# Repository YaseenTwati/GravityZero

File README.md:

# GravityZero

GravityZero is an Open Source STM32G473-based development board with two USB ports (Native & CH340 Serial), and access to nearly all the IO ports through the headers. alongside an onboard "NeoPixel" RGB LED.

More can be learned about it in my [Write Up Here](https://yaseen.ly/stm32g473-development-board-gravityzero/).

### Should you build one ?
Most probably not no, the microcontroller isn't cheap ( at the time of writing ), the pcb is 4 layer pcb which can most likely be reduced down to two, and there plenety of cheaper options out there.
This was designed for the experience & fun, which again you can learn more about in my write up.

---
### License 
<br />This work is licensed under a <a rel="license" href="http://creativecommons.org/licenses/by-sa/4.0/">Creative Commons Attribution-ShareAlike 4.0 International License</a>.

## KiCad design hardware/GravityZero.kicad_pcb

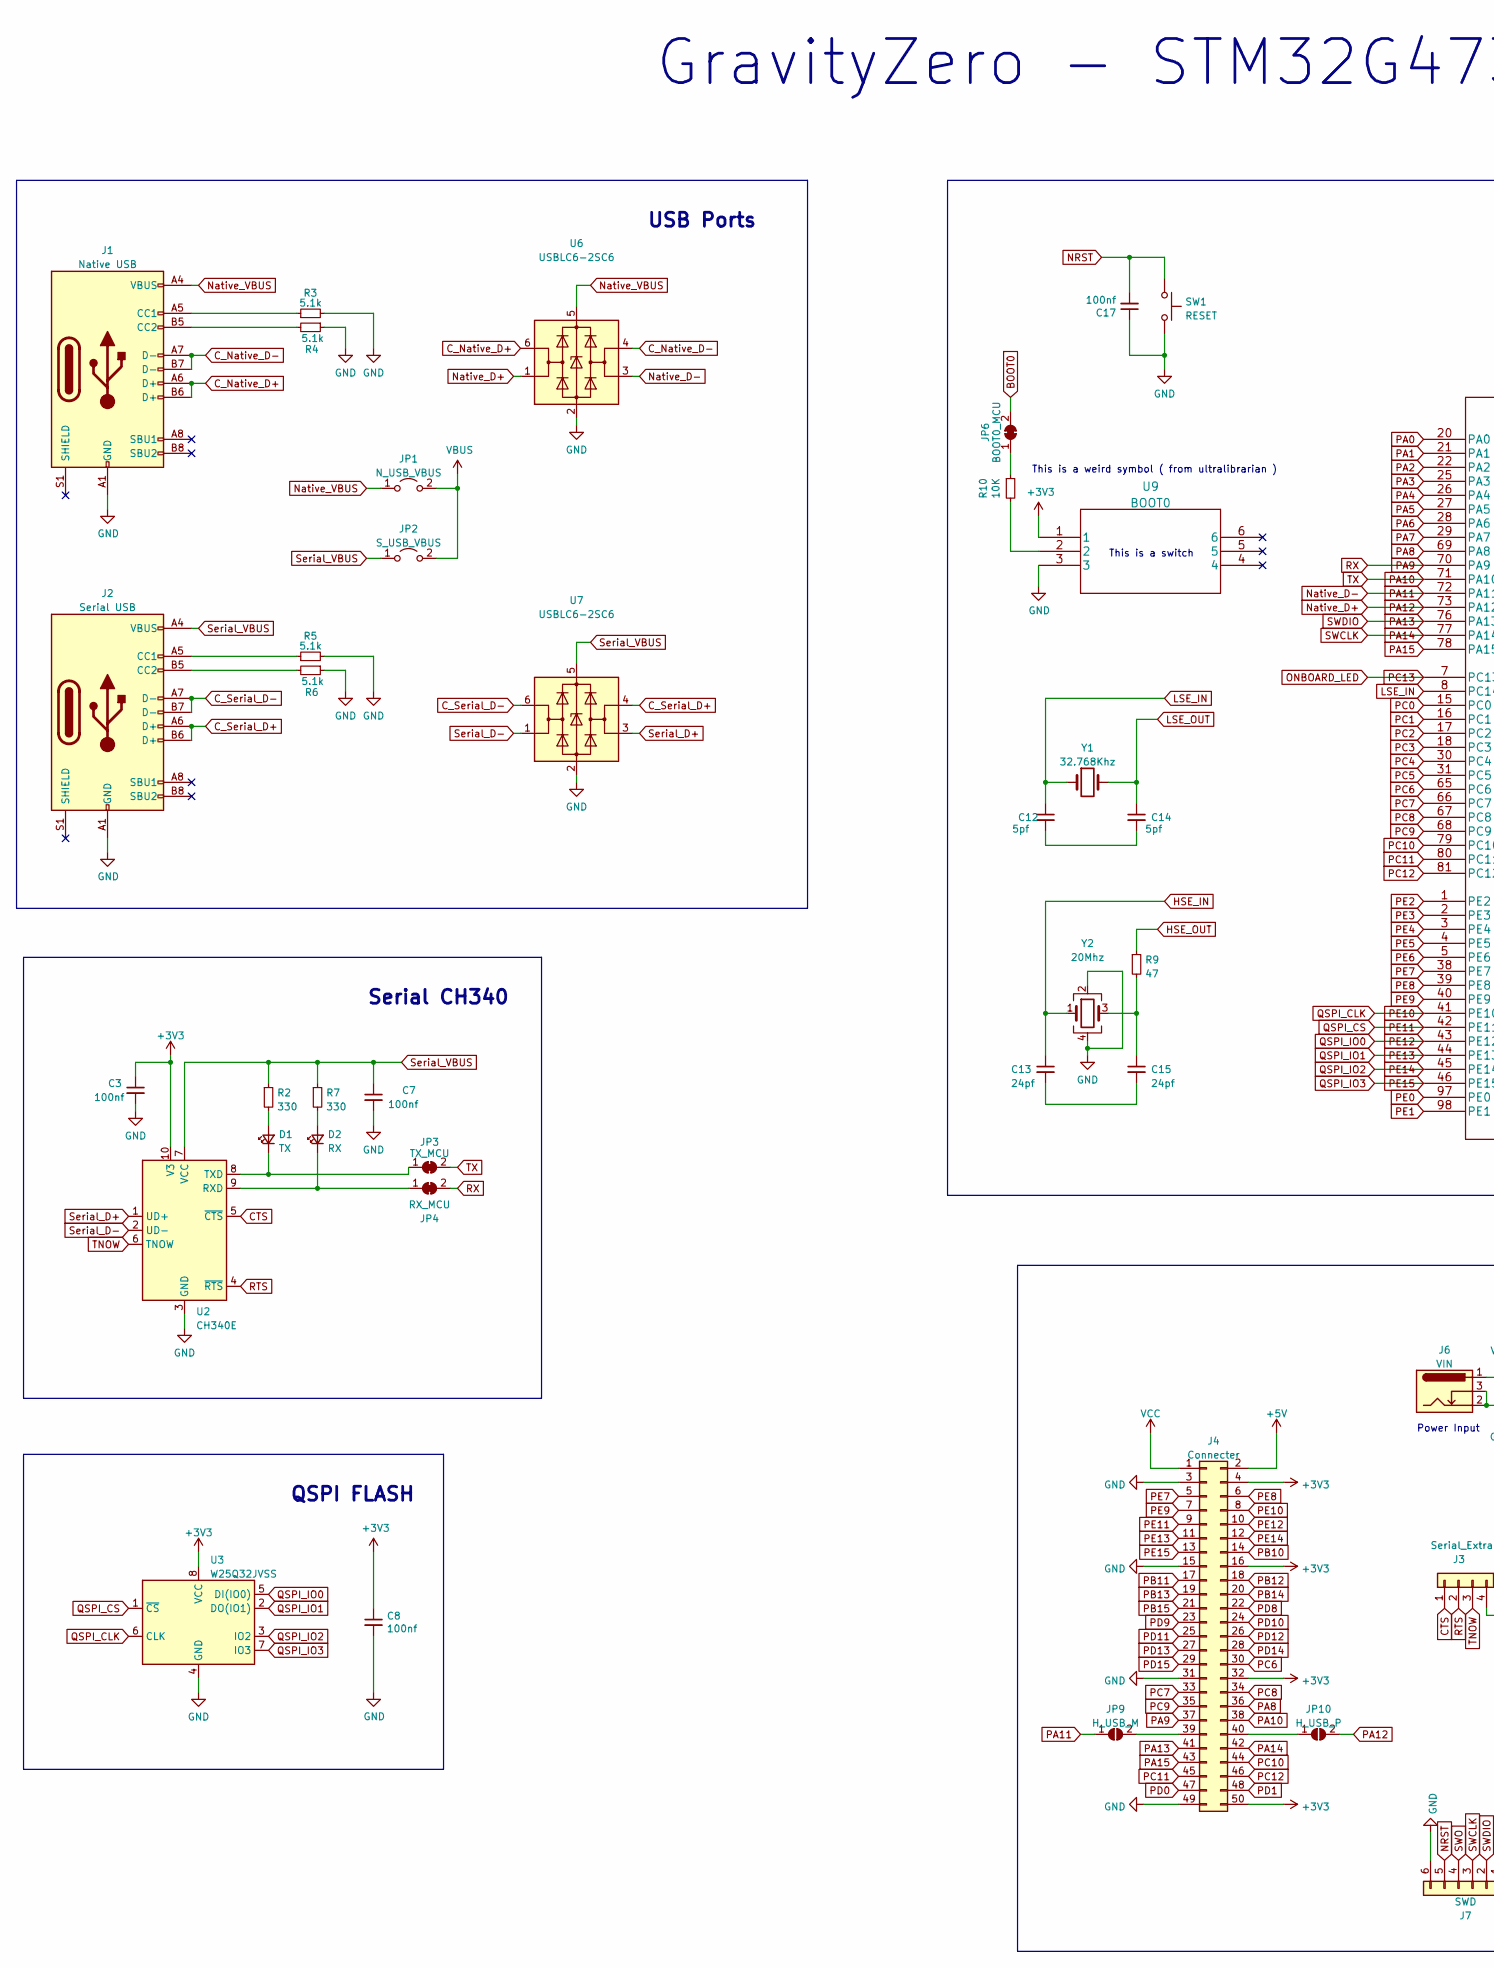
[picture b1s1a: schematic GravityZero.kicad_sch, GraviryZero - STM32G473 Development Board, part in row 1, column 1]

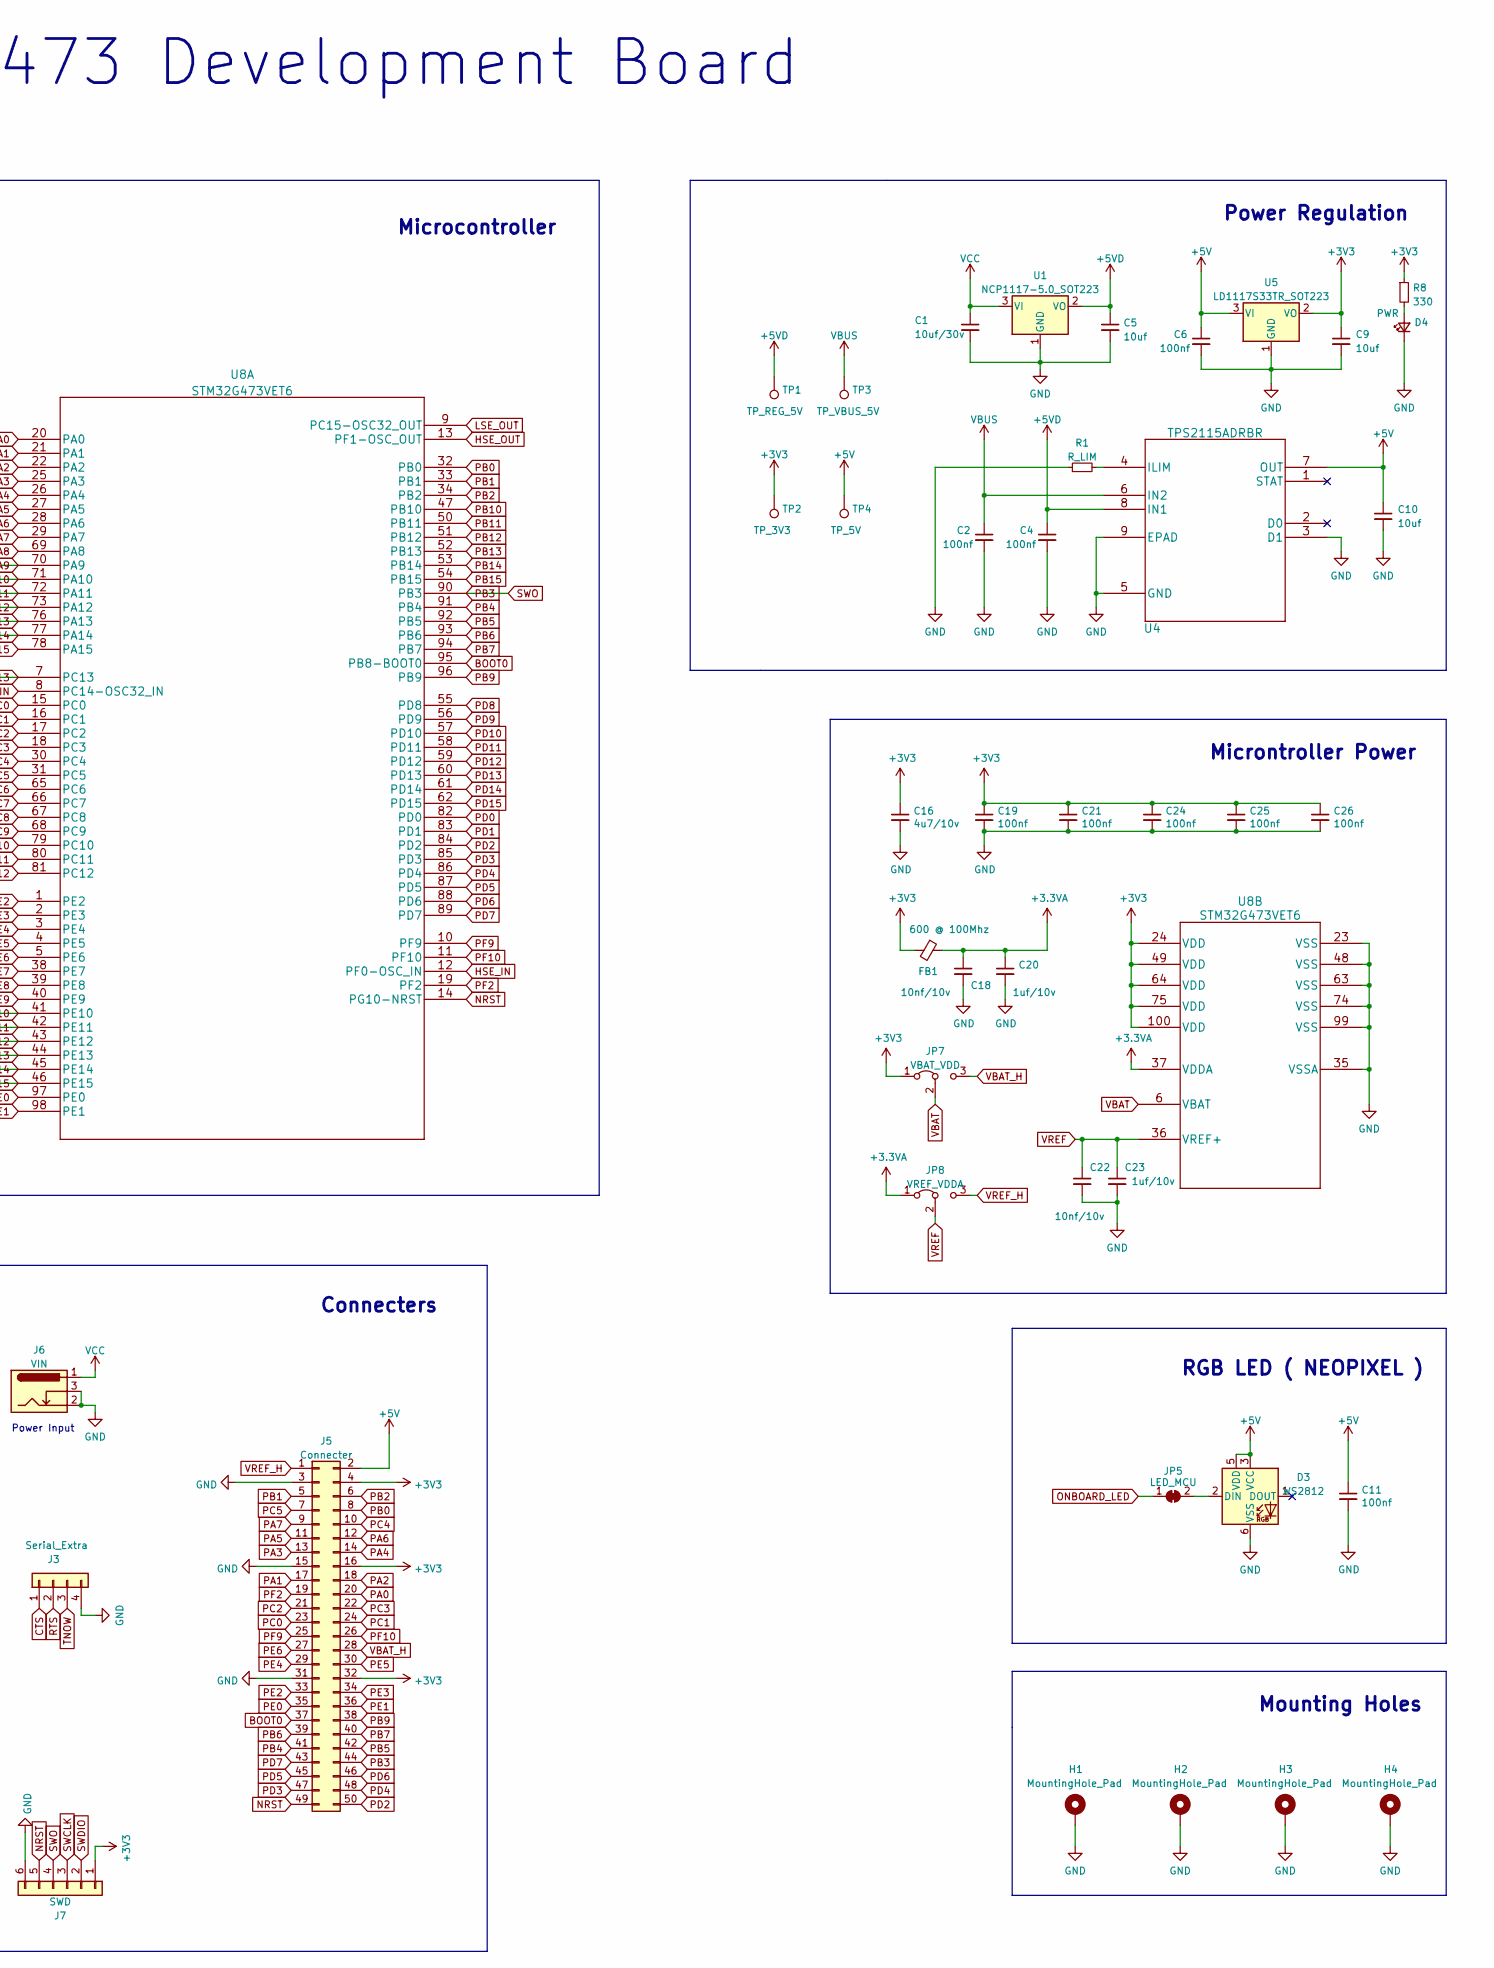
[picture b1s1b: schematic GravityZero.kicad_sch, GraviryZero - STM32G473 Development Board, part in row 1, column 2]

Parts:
C1: 10uf/30v; C_0805_2012Metric
C2, C3, C4, C6, C7, C8, C11, C17, C19, C21, C24, C25, C26: 100nf; C_0603_1608Metric
C5, C9, C10: 10uf; C_0603_1608Metric
C12, C14: 5pf; C_0603_1608Metric
C13, C15: 24pf; C_0603_1608Metric
C16: 4u7/10v; C_0603_1608Metric
C18, C22: 10nf/10v; C_0603_1608Metric
C20, C23: 1uf/10v; C_0603_1608Metric
D1: TX; LED_0603_1608Metric
D2: RX; LED_0603_1608Metric
D3: WS2812; LED_WS2812_PLCC6_5.0x5.0mm_P1.6mm
D4: PWR; LED_0603_1608Metric
FB1: 600 @ 100Mhz; L_0603_1608Metric
H1, H2, H3, H4: MountingHole_Pad; MountingHole_3.2mm_M3_Pad_Via
J1: Native USB; USB_C_Receptacle_HRO_TYPE-C-31-M-12
J2: Serial USB; USB_C_Receptacle_HRO_TYPE-C-31-M-12
J3: Serial_Extra; PinHeader_1x04_P2.54mm_Vertical
J4, J5: Connecter; PinHeader_2x25_P2.54mm_Vertical
J6: VIN; BarrelJack_Horizontal
J7: SWD; PinHeader_1x06_P2.54mm_Vertical
JP1: N_USB_VBUS; PinHeader_1x02_P2.54mm_Vertical
JP2: S_USB_VBUS; PinHeader_1x02_P2.54mm_Vertical
JP3: TX_MCU; SolderJumper-2_P1.3mm_Open_TrianglePad1.0x1.5mm
JP4: RX_MCU; SolderJumper-2_P1.3mm_Open_TrianglePad1.0x1.5mm
JP5: LED_MCU; SolderJumper-2_P1.3mm_Open_TrianglePad1.0x1.5mm
JP6: BOOT0_MCU; SolderJumper-2_P1.3mm_Open_TrianglePad1.0x1.5mm
JP7: VBAT_VDD; SolderJumper-3_P2.0mm_Open_TrianglePad1.0x1.5mm
JP8: VREF_VDDA; SolderJumper-3_P2.0mm_Open_TrianglePad1.0x1.5mm
JP9: H_USB_M; SolderJumper-2_P1.3mm_Open_TrianglePad1.0x1.5mm
JP10: H_USB_P; SolderJumper-2_P1.3mm_Open_TrianglePad1.0x1.5mm
R1: R_LIM; R_0603_1608Metric
R2, R7, R8: 330; R_0603_1608Metric
R3, R4, R5, R6: 5.1k; R_0603_1608Metric
R9: 47; R_0603_1608Metric
R10: 10K; R_0603_1608Metric
SW1: RESET; SW_PUSH_6mm
TP1: TP_REG_5V; TestPoint_Pad_D1.0mm
TP2: TP_3V3; TestPoint_Pad_D1.0mm
TP3: TP_VBUS_5V; TestPoint_Pad_D1.0mm
TP4: TP_5V; TestPoint_Pad_D1.0mm
U1: NCP1117-5.0_SOT223; SOT-223-3_TabPin2
U2: CH340E; MSOP-10_3x3mm_P0.5mm
U3: W25Q32JVSS; SOIC-8_5.23x5.23mm_P1.27mm
U4: TPS2115ADRBR
U5: LD1117S33TR_SOT223; SOT-223-3_TabPin2
U6, U7: USBLC6-2SC6; SOT-23-6
U8: STM32G473VET6; LQFP-100_14x14mm_P0.5mm
U9: BOOT0; SS-3235S-L2
Y1: 32.768Khz; Crystal_SMD_3215-2Pin_3.2x1.5mm
Y2: 20Mhz; Crystal_SMD_3225-4Pin_3.2x2.5mm

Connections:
+3.3VA: C18.1, C20.1, FB1.1, JP8.1 (A), U8.37 (VDDA)
+3V3: C3.1, C8.1, C9.1, C16.1, C19.1, C21.1, C24.1, C25.1, C26.1, FB1.2, J4.4, J4.16, J4.32, J4.50, J5.4, J5.16, J5.32, J7.1, JP7.1 (A), R8.1, TP2.1, U2.10 (V3), U3.8 (VCC), U5.2 (VO), U8.24 (VDD), U8.49 (VDD), U8.64 (VDD), U8.75 (VDD), U8.100 (VDD), U9.1
+5V: C6.1, C10.1, C11.1, D3.3 (VCC), D3.5 (VDD), J4.2, J5.2, TP4.1, U4.7 (OUT), U5.3 (VI)
+5VD: C4.1, C5.1, TP1.1, U1.2 (VO), U4.8 (IN1)
BOOT0: J5.37, JP6.2 (B), U8.95 (PB8-BOOT0); also elsewhere on the board
CTS: J3.1, U2.5 (~CTS)
C_Native_D+: J1.A6 (D+), J1.B6 (D+), U6.6 (I/O1)
C_Native_D-: J1.A7 (D-), J1.B7 (D-), U6.4 (I/O2)
C_Serial_D+: J2.A6 (D+), J2.B6 (D+), U7.4 (I/O2)
C_Serial_D-: J2.A7 (D-), J2.B7 (D-), U7.6 (I/O1)
GND: C1.2, C2.2, C3.2, C4.2, C5.2, C6.2, C7.2, C8.2, C9.2, C10.2, C11.2, C16.2, C17.1, C18.2, C19.2, C20.2, C21.2, C22.2, C23.2, C24.2, C25.2, C26.2, D3.6 (VSS), D4.1 (K), H1.1, H2.1, H3.1, H4.1, J1.A1 (GND), J1.A12 (GND), J1.B1 (GND), J1.B12 (GND), J2.A1 (GND), J2.A12 (GND), J2.B1 (GND), J2.B12 (GND), J3.4, J4.3, J4.15, J4.31, J4.49, J5.3, J5.15, J5.31, J6.2, J6.3, J7.6, R1.1, R3.2, R4.1, R5.2, R6.1, SW1.2, U1.1 (GND), U2.3 (GND), U3.4 (GND), U4.3 (D1), U4.5 (GND), U4.9 (EPAD), U5.1 (GND), U6.2 (GND), U7.2 (GND), U8.23 (VSS), U8.35 (VSSA), U8.48 (VSS), U8.63 (VSS), U8.74 (VSS), U8.99 (VSS), U9.3, Y2.2, Y2.4
HSE_IN: C13.1, U8.12 (PF0-OSC_IN), Y2.1
HSE_OUT: R9.1, U8.13 (PF1-OSC_OUT)
LSE_IN: C12.1, U8.8 (PC14-OSC32_IN), Y1.1
LSE_OUT: C14.1, U8.9 (PC15-OSC32_OUT), Y1.2
NRST: C17.2, J5.49, J7.5, SW1.1, U8.14 (PG10-NRST)
Native_D+: JP10.2 (B), U6.1 (I/O1), U8.73 (PA12)
Native_D-: JP9.1 (A), U6.3 (I/O2), U8.72 (PA11)
Native_VBUS: J1.A4 (VBUS), J1.A9 (VBUS), J1.B4 (VBUS), J1.B9 (VBUS), JP1.1 (A), U6.5 (VBUS)
unnamed: C12.2, C14.2
unnamed: C13.2, C15.2
unnamed: C15.1, R9.2, Y2.3
unnamed: D1.1 (K), JP3.1 (A), U2.8 (TXD)
unnamed: D1.2 (A), R2.2
unnamed: D2.1 (K), JP4.1 (A), U2.9 (RXD)
unnamed: D2.2 (A), R7.2
unnamed: D3.2 (DIN), JP5.2 (B)
unnamed: D4.2 (A), R8.2
unnamed: J1.A5 (CC1), R3.1
unnamed: J1.B5 (CC2), R4.2
unnamed: J2.A5 (CC1), R5.1
unnamed: J2.B5 (CC2), R6.2
unnamed: J4.39, JP9.2 (B)
unnamed: J4.40, JP10.1 (A)
unnamed 34: JP6.1 (A), R10.1; also elsewhere on the board
unnamed: R1.2, U4.4 (ILIM)
unnamed: R10.2, U9.2
ONBOARD_LED: JP5.1 (A), U8.7 (PC13)
PA0: J5.20, U8.20 (PA0)
PA1: J5.17, U8.21 (PA1)
PA2: J5.18, U8.22 (PA2)
PA3: J5.13, U8.25 (PA3)
PA4: J5.14, U8.26 (PA4)
PA5: J5.11, U8.27 (PA5)
PA6: J5.12, U8.28 (PA6)
PA7: J5.9, U8.29 (PA7)
PA8: J4.36, U8.69 (PA8)
PA9: J4.37, JP4.2 (B), U8.70 (PA9)
PA10: J4.38, JP3.2 (B), U8.71 (PA10)
PA13: J4.41, J7.2, U8.76 (PA13)
PA14: J4.42, J7.3, U8.77 (PA14)
PA15: J4.43, U8.78 (PA15)
PB0: J5.8, U8.32 (PB0)
PB1: J5.5, U8.33 (PB1)
PB2: J5.6, U8.34 (PB2)
PB3: J5.44, J7.4, U8.90 (PB3)
PB4: J5.41, U8.91 (PB4)
PB5: J5.42, U8.92 (PB5)
PB6: J5.39, U8.93 (PB6)
PB7: J5.40, U8.94 (PB7)
PB9: J5.38, U8.96 (PB9)
PB10: J4.14, U8.47 (PB10)
PB11: J4.17, U8.50 (PB11)
PB12: J4.18, U8.51 (PB12)
PB13: J4.19, U8.52 (PB13)
PB14: J4.20, U8.53 (PB14)
PB15: J4.21, U8.54 (PB15)
PC0: J5.23, U8.15 (PC0)
PC1: J5.24, U8.16 (PC1)
PC2: J5.21, U8.17 (PC2)
PC3: J5.22, U8.18 (PC3)
PC4: J5.10, U8.30 (PC4)
PC5: J5.7, U8.31 (PC5)
PC6: J4.30, U8.65 (PC6)
PC7: J4.33, U8.66 (PC7)
PC8: J4.34, U8.67 (PC8)
PC9: J4.35, U8.68 (PC9)
PC10: J4.44, U8.79 (PC10)
PC11: J4.45, U8.80 (PC11)
PC12: J4.46, U8.81 (PC12)
PD0: J4.47, U8.82 (PD0)
PD1: J4.48, U8.83 (PD1)
PD2: J5.50, U8.84 (PD2)
PD3: J5.47, U8.85 (PD3)
PD4: J5.48, U8.86 (PD4)
PD5: J5.45, U8.87 (PD5)
PD6: J5.46, U8.88 (PD6)
PD7: J5.43, U8.89 (PD7)
PD8: J4.22, U8.55 (PD8)
PD9: J4.23, U8.56 (PD9)
PD10: J4.24, U8.57 (PD10)
PD11: J4.25, U8.58 (PD11)
PD12: J4.26, U8.59 (PD12)
PD13: J4.27, U8.60 (PD13)
PD14: J4.28, U8.61 (PD14)
PD15: J4.29, U8.62 (PD15)
PE0: J5.35, U8.97 (PE0)
PE1: J5.36, U8.98 (PE1)
PE2: J5.33, U8.1 (PE2)
PE3: J5.34, U8.2 (PE3)
PE4: J5.29, U8.3 (PE4)
PE5: J5.30, U8.4 (PE5)
PE6: J5.27, U8.5 (PE6)
PE7: J4.5, U8.38 (PE7)
PE8: J4.6, U8.39 (PE8)
PE9: J4.7, U8.40 (PE9)
PE10: J4.8, U3.6 (CLK), U8.41 (PE10)
PE11: J4.9, U3.1 (~CS), U8.42 (PE11)
PE12: J4.10, U3.5 (DI(IO0)), U8.43 (PE12)
PE13: J4.11, U3.2 (DO(IO1)), U8.44 (PE13)
PE14: J4.12, U3.3 (IO2), U8.45 (PE14)
PE15: J4.13, U3.7 (IO3), U8.46 (PE15)
PF2: J5.19, U8.19 (PF2)
PF9: J5.25, U8.10 (PF9)
PF10: J5.26, U8.11 (PF10)
RTS: J3.2, U2.4 (~RTS)
Serial_D+: U2.1 (UD+), U7.3 (I/O2)
Serial_D-: U2.2 (UD-), U7.1 (I/O1)
Serial_VBUS: C7.1, J2.A4 (VBUS), J2.A9 (VBUS), J2.B4 (VBUS), J2.B9 (VBUS), JP2.1 (A), R2.1, R7.1, U2.7 (VCC), U7.5 (VBUS)
TNOW: J3.3, U2.6 (TNOW)
VBAT: JP7.2 (C), U8.6 (VBAT)
VBAT_H: J5.28, JP7.3 (B)
VBUS: C2.1, JP1.2 (B), JP2.2 (B), TP3.1, U4.6 (IN2)
VCC: C1.1, J4.1, J6.1, U1.3 (VI)
VREF: C22.1, C23.1, JP8.2 (C), U8.36 (VREF+)
VREF_H: J5.1, JP8.3 (B)

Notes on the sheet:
Microntroller Power
Power Input
GravityZero - STM32G473 Development Board
Microcontroller
QSPI FLASH
This is a weird symbol ( from ultralibrarian )
Serial CH340
USB Ports
Mounting Holes
RGB LED ( NEOPIXEL )
Connecters
Power Regulation
This is a switch

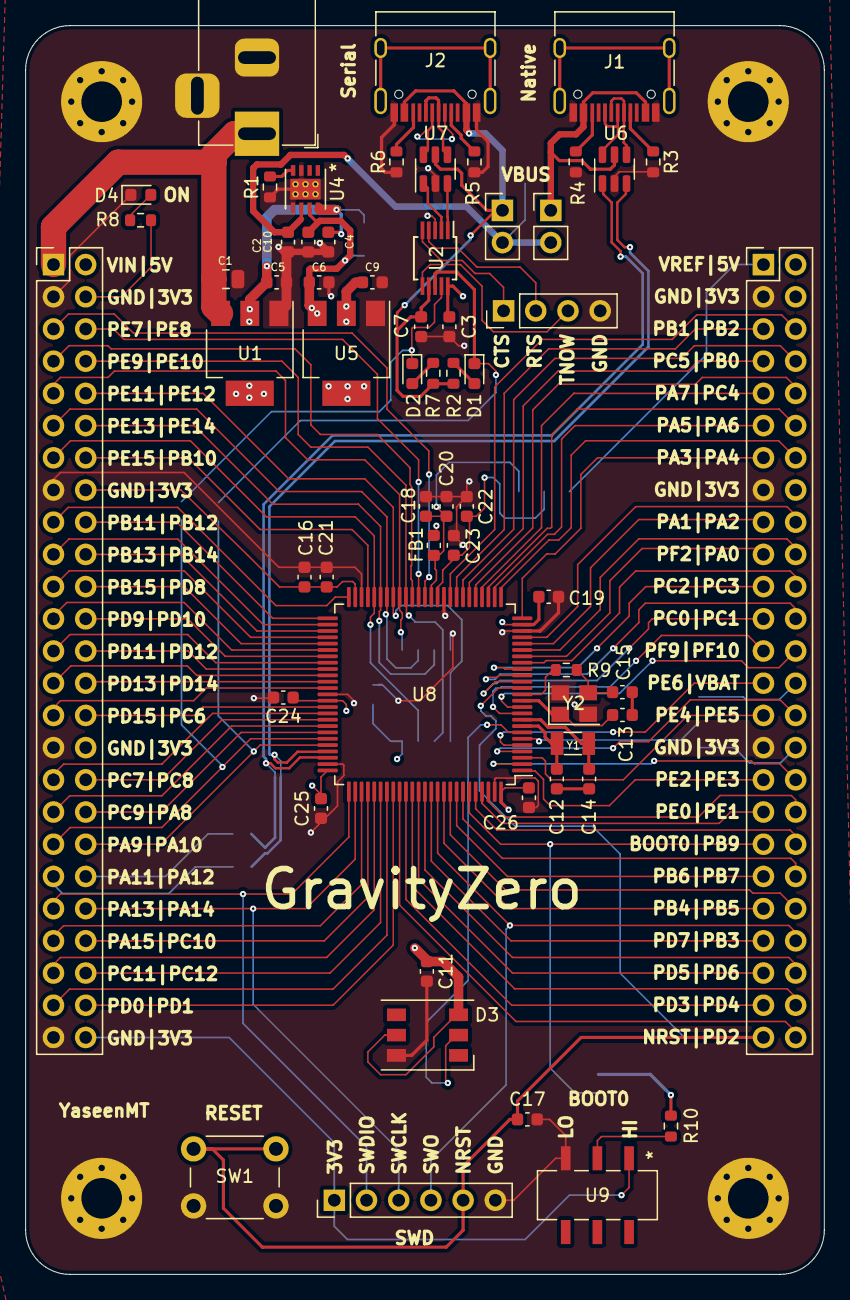
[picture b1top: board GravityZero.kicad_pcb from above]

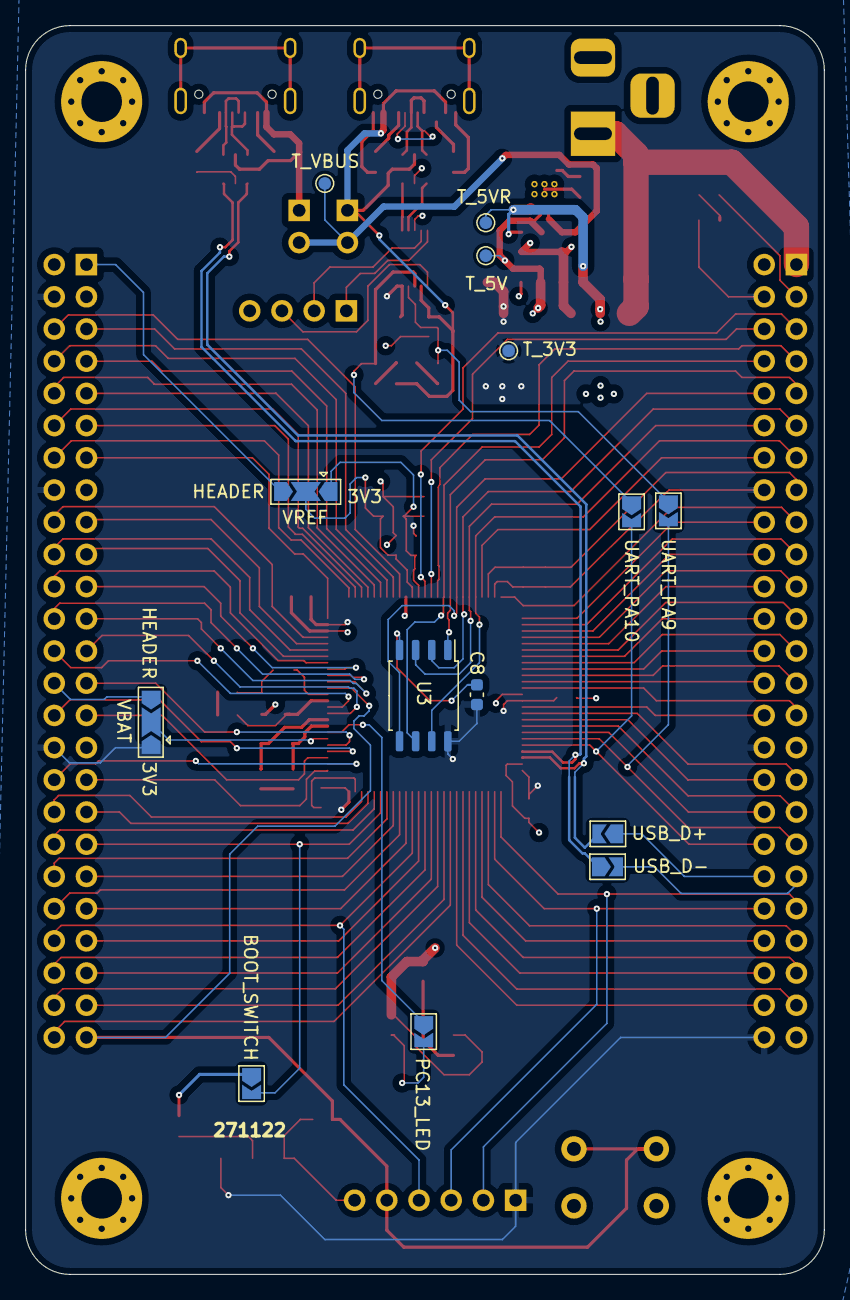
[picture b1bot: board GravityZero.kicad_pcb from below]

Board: 4 copper layers, 63.0 x 98.5 mm, 78 parts (14 on the bottom side), 126 nets.

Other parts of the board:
BOOT_SWITCH: BOOT0_MCU; SolderJumper-2_P1.3mm_Open_TrianglePad1.0x1.5mm

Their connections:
BOOT0: BOOT_SWITCH.2 (B); also elsewhere on the board
unnamed 34: BOOT_SWITCH.1 (A); also elsewhere on the board
